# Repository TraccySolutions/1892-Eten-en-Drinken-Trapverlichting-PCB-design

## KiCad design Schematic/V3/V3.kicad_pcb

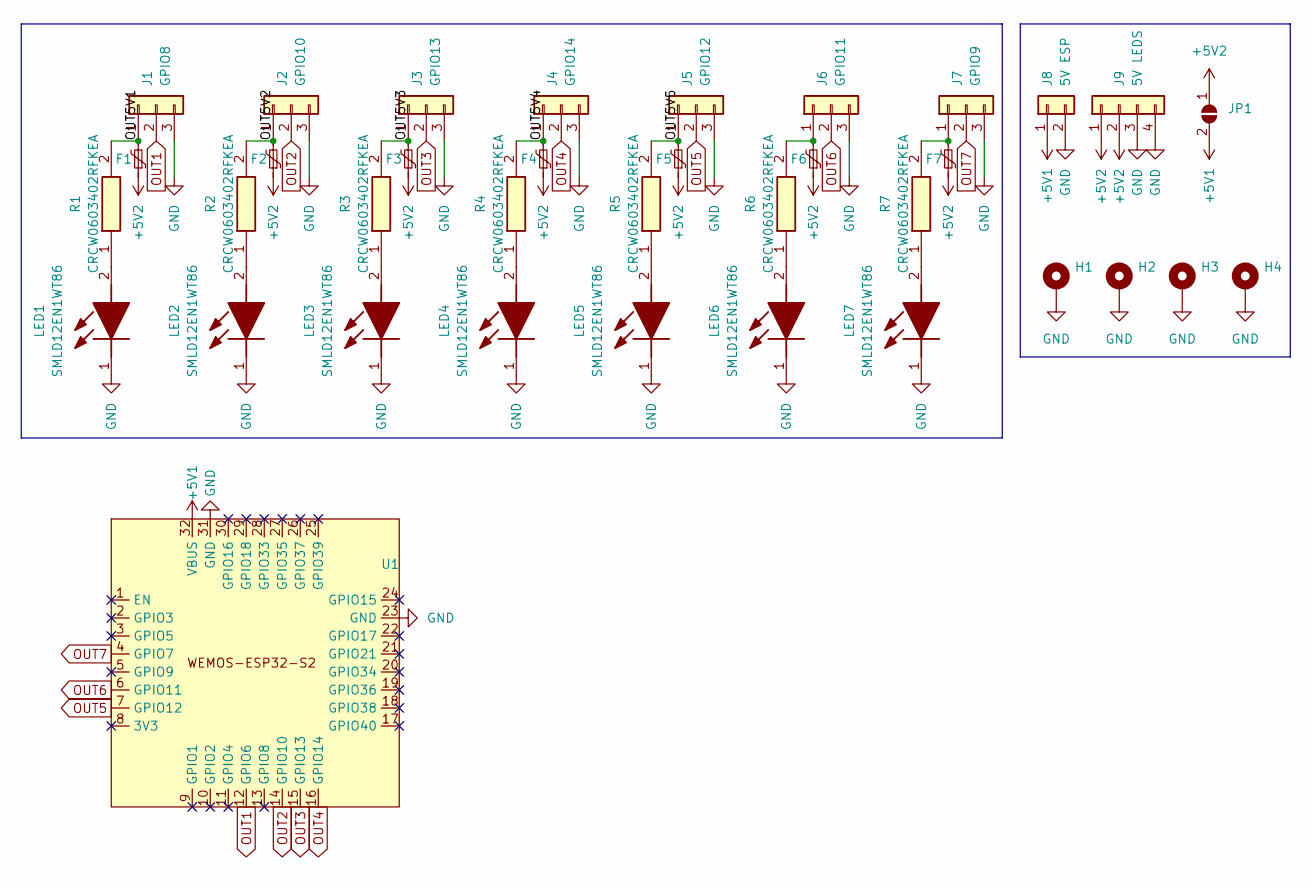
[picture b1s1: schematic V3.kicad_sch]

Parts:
F1, F2, F3, F4, F5, F6, F7: Polyfuse_Small; 1812L010DR; Mouser Part Number 652-MF-MSMF260-2
H1, H2, H3, H4: MountingHole_Pad; MountingHole_3.2mm_M3_ISO14580_Pad
J1: GPIO8; Custom solderWire 1x03 with relief
J2: GPIO10; Custom solderWire 1x03 with relief
J3: GPIO13; Custom solderWire 1x03 with relief
J4: GPIO14; Custom solderWire 1x03 with relief
J5: GPIO12; Custom solderWire 1x03 with relief
J6: GPIO11; Custom solderWire 1x03 with relief
J7: GPIO9; Custom solderWire 1x03 with relief
J8: 5V ESP; SolderWire-0.25sqmm_1x02_P4.2mm_D0.65mm_OD1.7mm_Relief
J9: 5V LEDS; Custom SolderWire 1x04 with relief
JP1: SolderJumper_2_Open; SolderJumper-2_P1.3mm_Open_TrianglePad1.0x1.5mm
LED1, LED2, LED3, LED4, LED5, LED6, LED7: SMLD12EN1WT86; LEDM168X65N; Mouser Part Number 755-SMLD12EN1WT86
R1, R2, R3, R4, R5, R6, R7: CRCW0603402RFKEA; RESC1608X50N; Mouser Part Number 71-CRCW0603-402-E3
U1: WEMOS-ESP32-S2

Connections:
+5V1: J8.1, JP1.2 (B), U1.32 (VBUS)
+5V2: F1.1, F2.1, F3.1, F4.1, F5.1, F6.1, F7.1, J9.1, J9.2, JP1.1 (A)
/OUT5V1: F1.2, J1.1, R1.2
/OUT5V2: F2.2, J2.1, R2.2
/OUT5V3: F3.2, J3.1, R3.2
/OUT5V4: F4.2, J4.1, R4.2
/OUT5V5: F5.2, J5.1, R5.2
GND: H1.1, H2.1, H3.1, H4.1, J1.3, J2.3, J3.3, J4.3, J5.3, J6.3, J7.3, J8.2, J9.3, J9.4, LED1.1 (K), LED2.1 (K), LED3.1 (K), LED4.1 (K), LED5.1 (K), LED6.1 (K), LED7.1 (K), U1.23 (GND), U1.31 (GND)
unnamed: F6.2, J6.1, R6.2
unnamed: F7.2, J7.1, R7.2
unnamed: LED1.2 (A), R1.1
unnamed: LED2.2 (A), R2.1
unnamed: LED3.2 (A), R3.1
unnamed: LED4.2 (A), R4.1
unnamed: LED5.2 (A), R5.1
unnamed: LED6.2 (A), R6.1
unnamed: LED7.2 (A), R7.1
OUT1: J1.2, U1.12 (GPIO6)
OUT2: J2.2, U1.14 (GPIO10)
OUT3: J3.2, U1.15 (GPIO13)
OUT4: J4.2, U1.16 (GPIO14)
OUT5: J5.2, U1.7 (GPIO12)
OUT6: J6.2, U1.6 (GPIO11)
OUT7: J7.2, U1.4 (GPIO7)

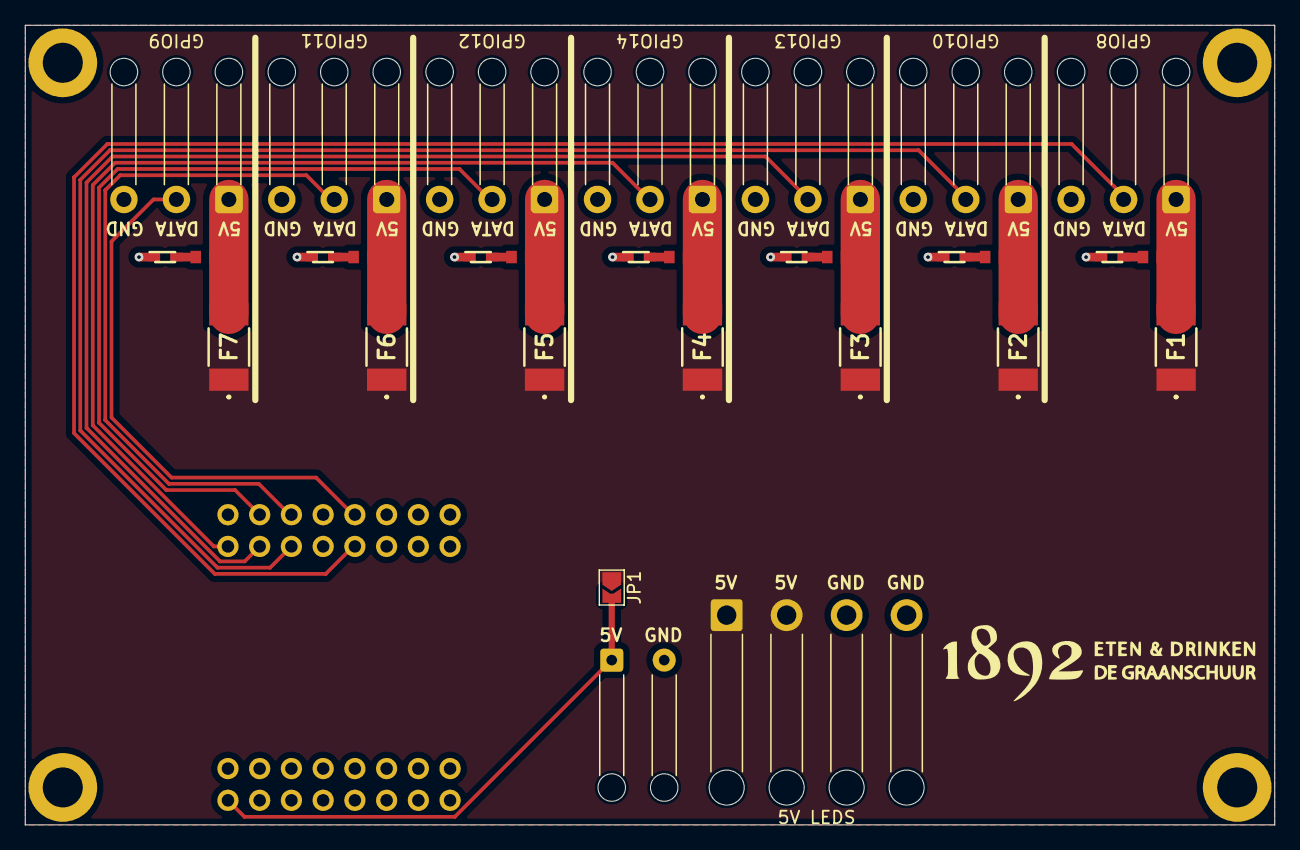
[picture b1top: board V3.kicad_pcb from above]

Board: 2 copper layers, 100.0 x 64.0 mm, 36 parts (0 on the bottom side), 24 nets.

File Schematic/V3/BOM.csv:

"Reference","Qty","Manufacturer_Name","Manufacturer_Part_Number","Mouser Part Number"
"F1,F2,F3,F4,F5,F6,F7","7","","MF-MSMF260-2 ","652-MF-MSMF260-2 "
"LED1,LED2,LED3,LED4,LED5,LED6,LED7","7","ROHM Semiconductor","SMLD12EN1WT86","755-SMLD12EN1WT86"
"R1,R2,R3,R4,R5,R6,R7","7","Vishay","CRCW0603402RFKEA","71-CRCW0603-402-E3"

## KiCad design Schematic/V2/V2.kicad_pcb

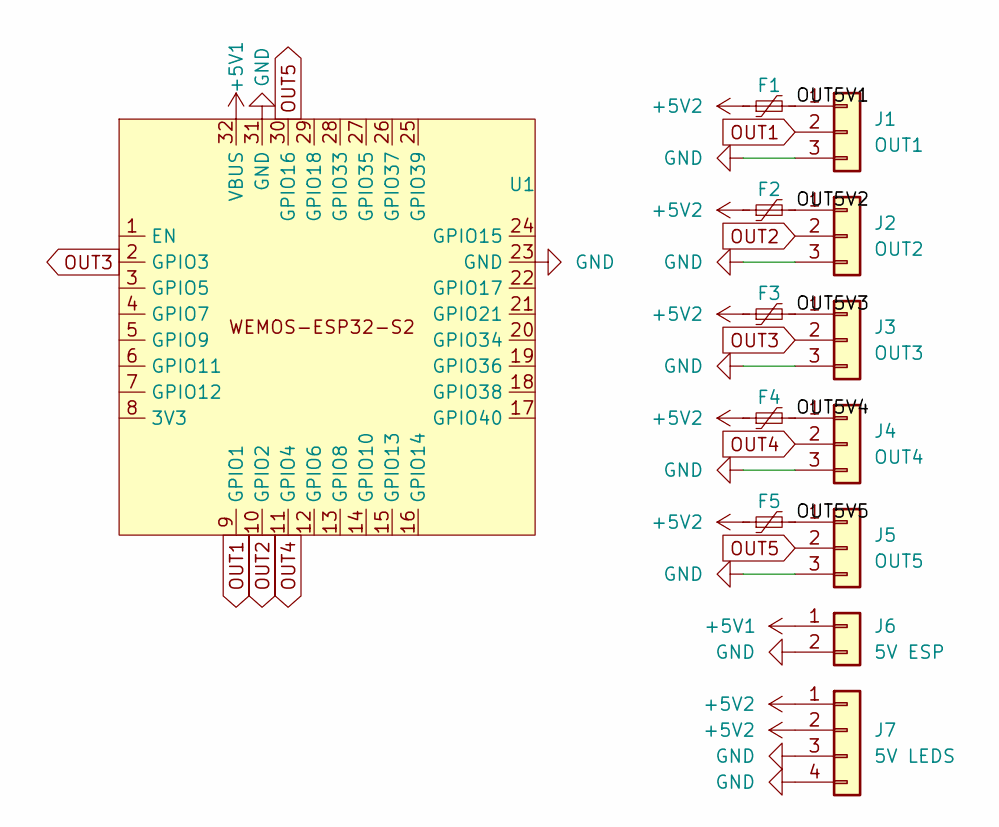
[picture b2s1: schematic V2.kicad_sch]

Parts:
F1, F2, F3, F4, F5: Polyfuse_Small; 1812L010DR
J1: OUT1; SolderWire-0.25sqmm_1x03_P4.2mm_D0.65mm_OD1.7mm_Relief
J2: OUT2; SolderWire-0.25sqmm_1x03_P4.2mm_D0.65mm_OD1.7mm_Relief
J3: OUT3; SolderWire-0.25sqmm_1x03_P4.2mm_D0.65mm_OD1.7mm_Relief
J4: OUT4; SolderWire-0.25sqmm_1x03_P4.2mm_D0.65mm_OD1.7mm_Relief
J5: OUT5; SolderWire-0.25sqmm_1x03_P4.2mm_D0.65mm_OD1.7mm_Relief
J6: 5V ESP; SolderWire-0.25sqmm_1x02_P4.2mm_D0.65mm_OD1.7mm_Relief
J7: 5V LEDS; SolderWire-0.75sqmm_1x04_P4.8mm_D1.25mm_OD2.3mm_Relief
U1: WEMOS-ESP32-S2

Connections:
+5V1: J6.1, U1.32 (VBUS)
+5V2: F1.1, F2.1, F3.1, F4.1, F5.1, J7.1, J7.2
/OUT5V1: F1.2, J1.1
/OUT5V2: F2.2, J2.1
/OUT5V3: F3.2, J3.1
/OUT5V4: F4.2, J4.1
/OUT5V5: F5.2, J5.1
GND: J1.3, J2.3, J3.3, J4.3, J5.3, J6.2, J7.3, J7.4, U1.23 (GND), U1.31 (GND)
OUT1: J1.2, U1.9 (GPIO1)
OUT2: J2.2, U1.10 (GPIO2)
OUT3: J3.2, U1.2 (GPIO3)
OUT4: J4.2, U1.11 (GPIO4)
OUT5: J5.2, U1.30 (GPIO16)

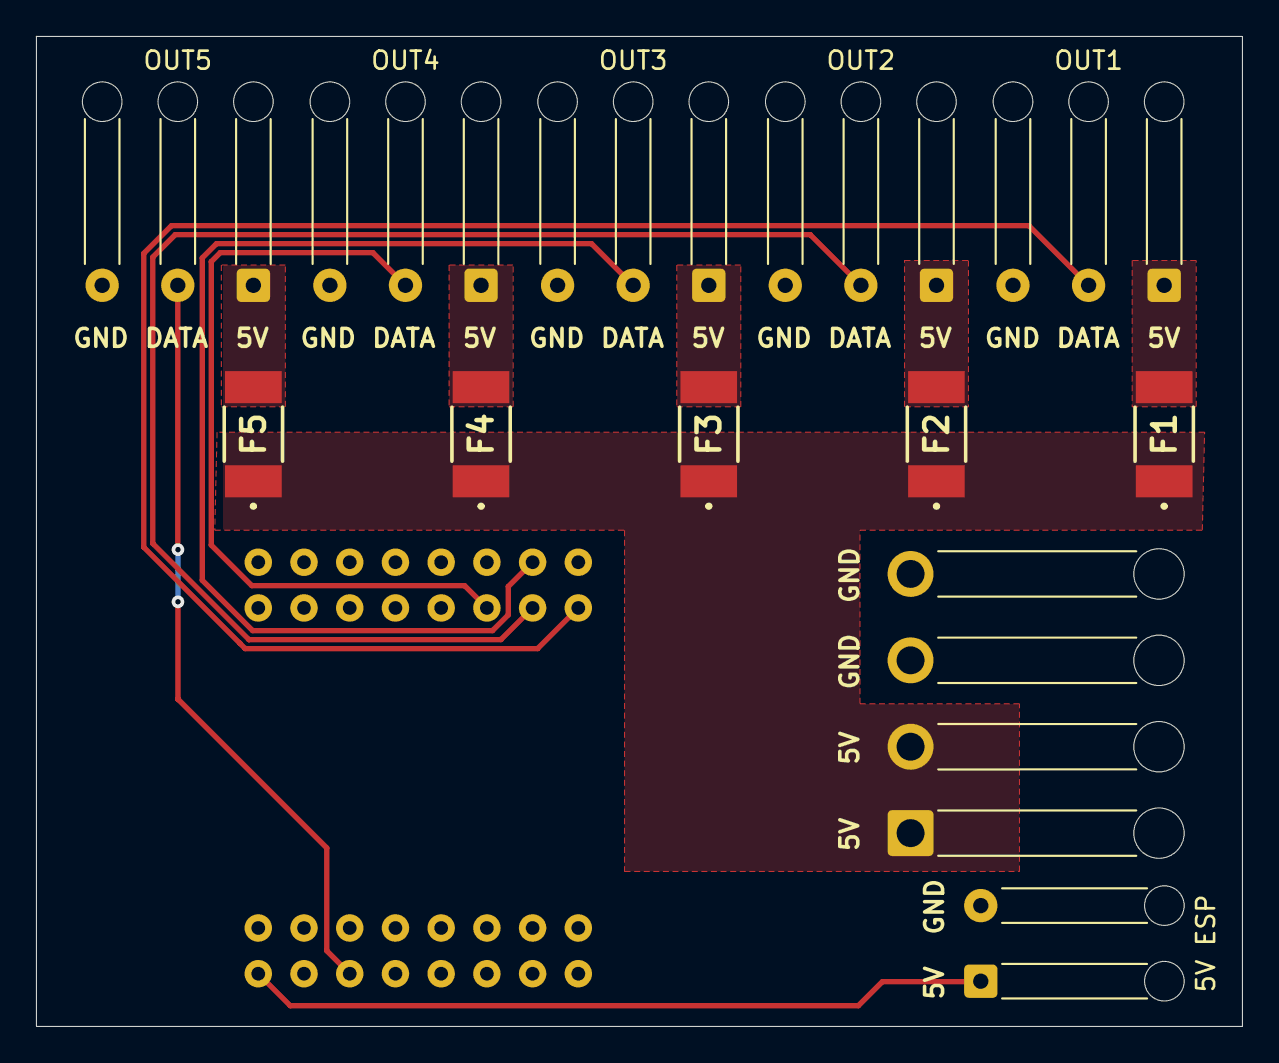
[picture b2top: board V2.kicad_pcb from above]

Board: 2 copper layers, 67.0 x 55.0 mm, 13 parts (0 on the bottom side), 13 nets.

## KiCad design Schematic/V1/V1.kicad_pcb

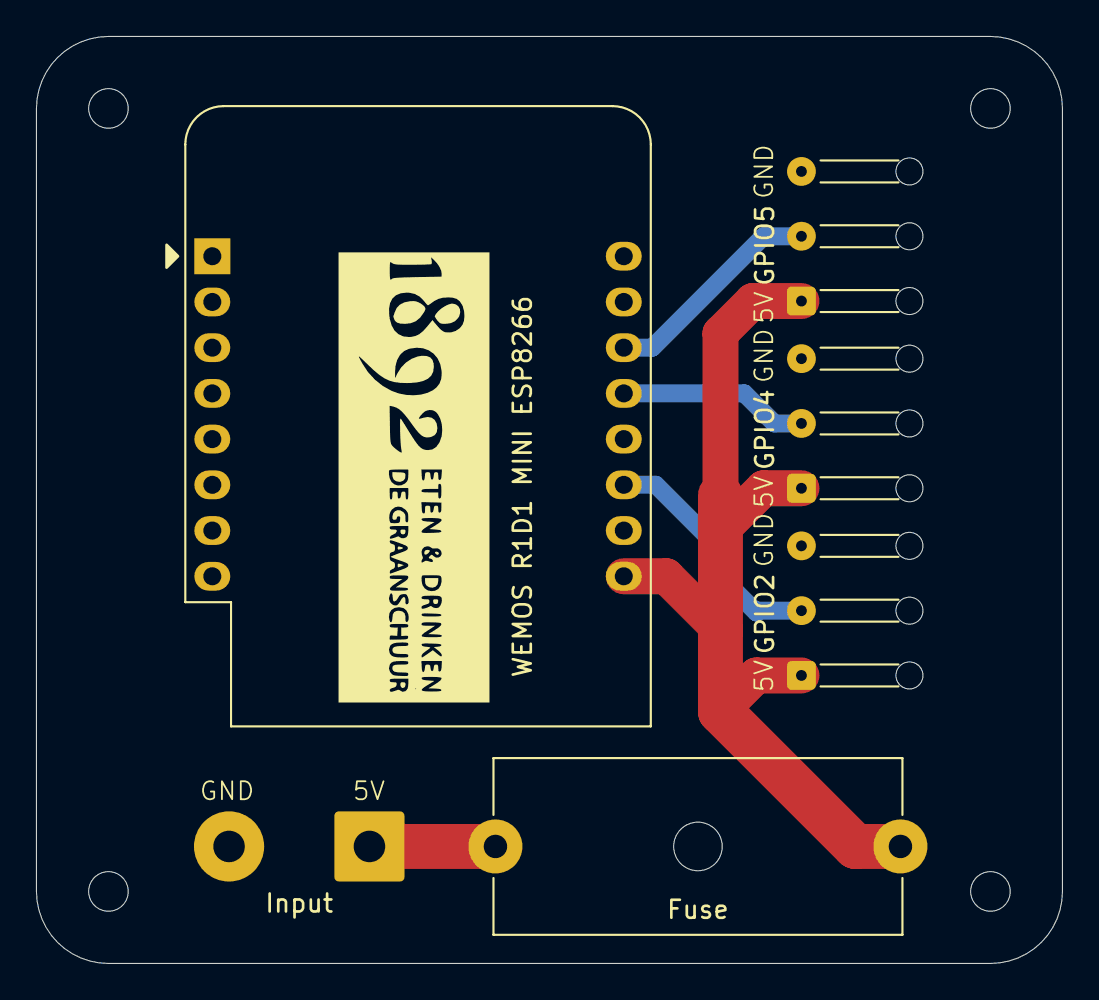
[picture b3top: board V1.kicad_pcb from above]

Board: 2 copper layers, 57.0 x 51.5 mm, 10 parts (0 on the bottom side), 6 nets.

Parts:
Fuse: Fuse; Fuseholder_Cylinder-5x20mm_Schurter_0031_8201_Horizontal_Op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
GPIO2, GPIO4, GPIO5: Conn_01x03_Socket; SolderWire-0.1sqmm_1x03_P3.6mm_D0.4mm_OD1mm_Relief
H1, H2, H3, H4: MountingHole; MountingHole_2.2mm_M2
Input: Conn_01x02_Socket; SolderWire-1sqmm_1x02_P7.8mm_D1.4mm_OD3.9mm
WEMOS R1D1 MINI ESP8266: WeMos_D1_mini; WEMOS_D1_mini_light

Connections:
+5V: Fuse.1, GPIO2.1, GPIO4.1, GPIO5.1, WEMOS R1D1 MINI ESP8266.9 (5V)
D1: GPIO5.2, WEMOS R1D1 MINI ESP8266.14 (SCL/D1)
D2: GPIO4.2, WEMOS R1D1 MINI ESP8266.13 (SDA/D2)
D4: GPIO2.2, WEMOS R1D1 MINI ESP8266.11 (D4)
GND: GPIO2.3, GPIO4.3, GPIO5.3, Input.2, WEMOS R1D1 MINI ESP8266.10 (GND)
unnamed: Fuse.2, Input.1

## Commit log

2024-04-18 added img and pcb
2024-07-02 Started V2
2024-07-02 Added V2
2024-07-02 Added prduciton files
2024-08-13 Added support for two 18 AWG wires as 5V input to allow 14A and updated traces as needed.
2024-08-20 Added V3
    Added two additional outputs.
    Added SolderPad for ESP power.
    Increased hole sizes for outputs (0,85 -> 1,2mm) and esp (0,762 -> 1,0mm).
    Added power indicator leds after fuses.
    Did not change Fuse size due to cost. (20 EUR) and from 2.6A to 3A is not that important I think.
    Should look for cheaper leds.
2024-08-20 Updated Production files
    Correct bom is the one not in the production folder.
2024-08-25 Added project specific library
2024-08-28 Just some backups
2024-12-12 Backups idk why
